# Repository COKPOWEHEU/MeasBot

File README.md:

# MeasBot
Automatization system for measures by scientific devices

Инструкция по тестированию:
=== Linux ===
Запускаете ./prog64 [script]
Если script не указан, будет использован дефолтный data/script.lua

=== Windows ===
Копируете core\res\prog32.exe в mingw_dll\res32.exe с заменой
Копируете в каталог modules\lib\lib\dyn (возможно, понадобится заменить файл dyn каталогом с тем же именем) следующие файлы с заменой имени:
modules\e24\res\prog32.dll -> e24.dll
modules\mygui_gtk\res\prog32.dll -> mygui_gtk.dll
modules\tty\res\prog32.dll -> tty.dll
После чего запускаете mingw_dll\prog32.exe [script]
Если script не указан, будет использован дефолтный data\script.lua

Данный геморрой связан с тем, что программа находится в начальной стадии разработки и особого внимания эргономике не уделялось.

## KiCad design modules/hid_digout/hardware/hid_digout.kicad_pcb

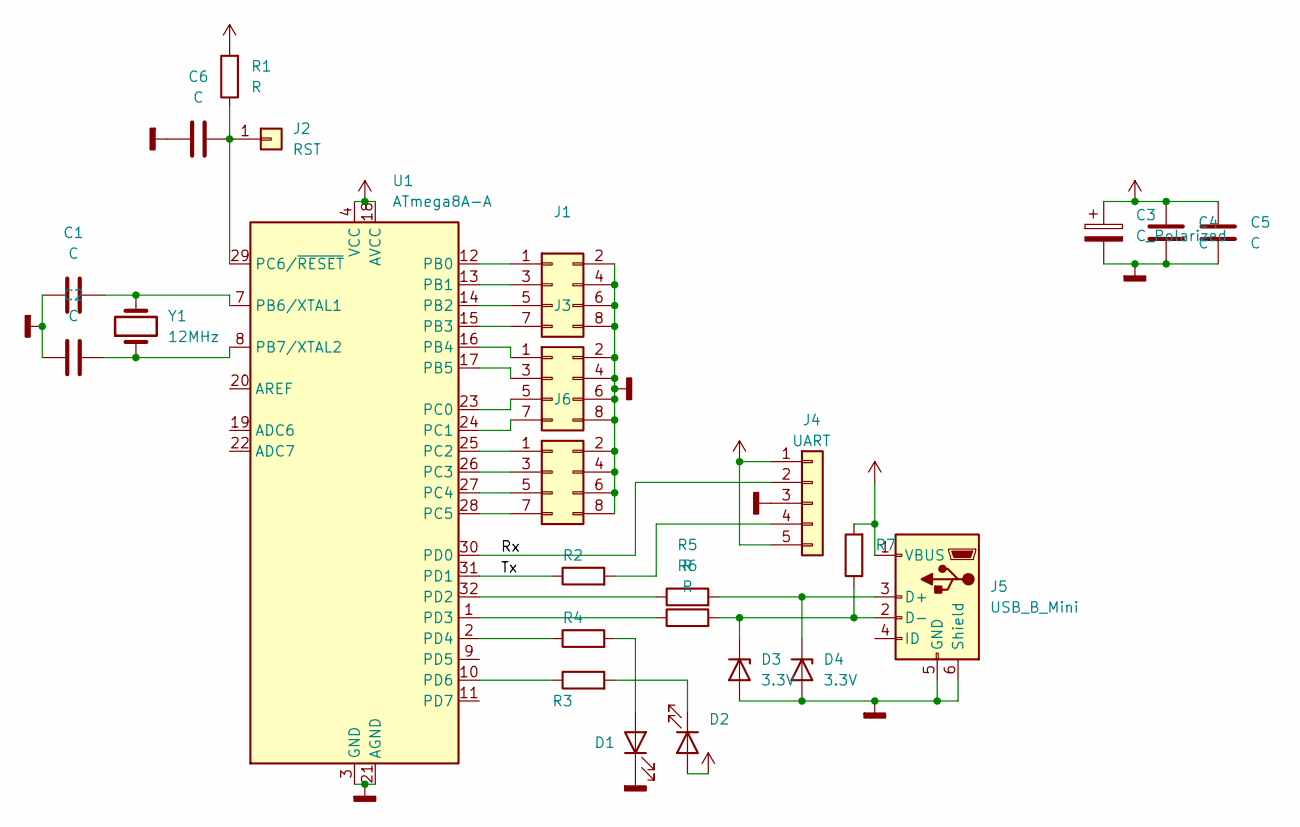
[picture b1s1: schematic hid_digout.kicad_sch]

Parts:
C1, C2: C; C_Disc_D3.4mm_W2.1mm_P2.50mm
C3: C_Polarized; CP_Radial_D10.0mm_P5.00mm
C4, C5: C; C_Disc_D5.0mm_W2.5mm_P5.00mm
C6: C; C_1206_3216Metric
D1, D2: LED; LED_D5.0mm_Horizontal_O3.81mm_Z9.0mm
D3, D4: 3.3V; D_5W_P10.16mm_Horizontal
J1, J3, J6: Conn_02x04_Odd_Even; PinHeader_2x04_P2.54mm_Horizontal
J2: RST; PinHeader_1x01_P2.54mm_Vertical
J4: UART; PinHeader_1x05_P2.54mm_Horizontal
J5: USB_B_Mini; USB-mini
R1, R2, R3, R4, R5, R6, R7: R; R_0805_2012Metric
U1: ATmega8A-A; TQFP-32_7x7mm_P0.8mm
Y1: 12MHz; Crystal_HC49-U_Vertical

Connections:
/Rx: J4.2, U1.30 (PD0)
/Tx: R2.1, U1.31 (PD1)
GNDD: C1.1, C2.1, C3.2, C4.1, C5.1, C6.1, D1.1 (K), D3.2 (A), D4.2 (A), J1.2, J1.4, J1.6, J1.8, J3.2, J3.4, J3.6, J3.8, J4.3, J5.5 (GND), J5.6 (Shield), J6.2, J6.4, J6.6, J6.8, U1.3 (GND), U1.5 (GND), U1.21 (AGND)
unnamed: C1.2, U1.7 (PB6/XTAL1), Y1.2
unnamed: C2.2, U1.8 (PB7/XTAL2), Y1.1
unnamed: D2.1 (K), R3.2
unnamed: D3.1 (K), J5.2 (D-), R6.2, R7.1
unnamed: D4.1 (K), J5.3 (D+), R5.2
unnamed: J4.4, R2.2
unnamed: C6.2, J2.1, R1.1, U1.29 (PC6/~RESET)
unnamed: R3.1, U1.10 (PD6)
unnamed: D1.2 (A), R4.2
unnamed: R5.1, U1.32 (PD2)
unnamed: R6.1, U1.1 (PD3)
unnamed: R4.1, U1.2 (PD4)
unnamed: J1.1, U1.12 (PB0)
unnamed: J1.3, U1.13 (PB1)
unnamed: J1.5, U1.14 (PB2)
unnamed: J1.7, U1.15 (PB3)
unnamed: J3.1, U1.16 (PB4)
unnamed: J3.3, U1.17 (PB5)
unnamed: J3.5, U1.23 (PC0)
unnamed: J3.7, U1.24 (PC1)
unnamed: J6.1, U1.25 (PC2)
unnamed: J6.3, U1.26 (PC3)
unnamed: J6.5, U1.27 (PC4)
unnamed: J6.7, U1.28 (PC5)
VCC: C3.1, C4.2, C5.2, D2.2 (A), J4.1, J4.5, J5.1 (VBUS), R1.2, R7.2, U1.4 (VCC), U1.6 (VCC), U1.18 (AVCC)

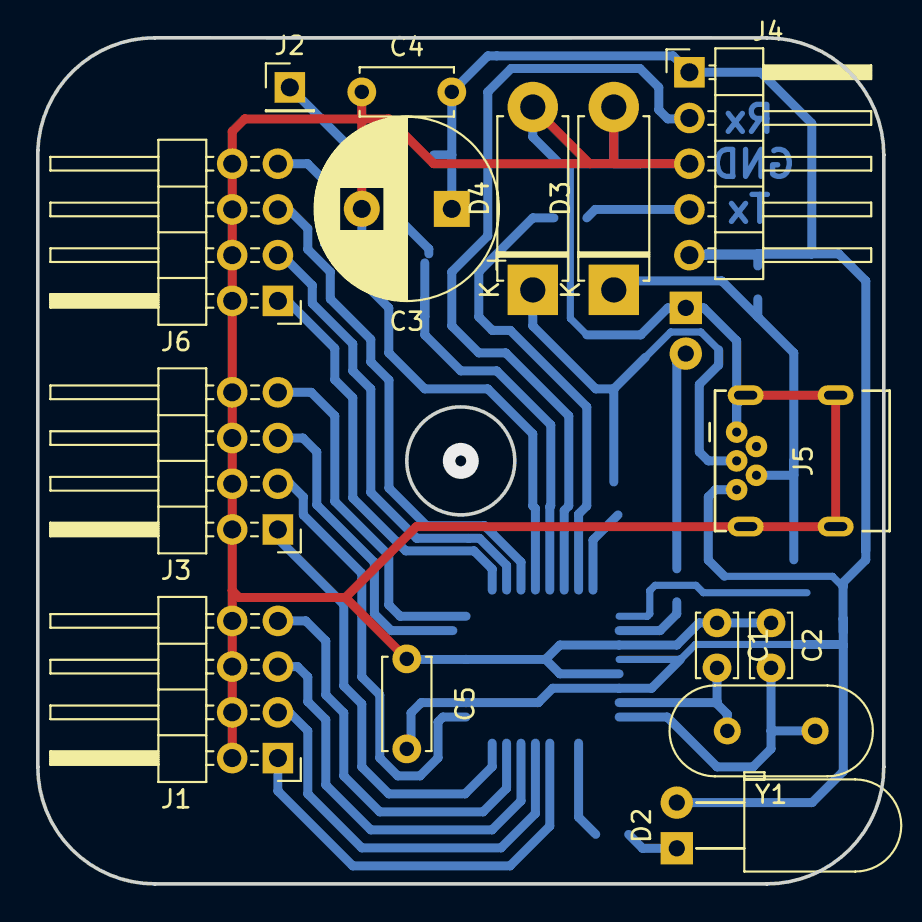
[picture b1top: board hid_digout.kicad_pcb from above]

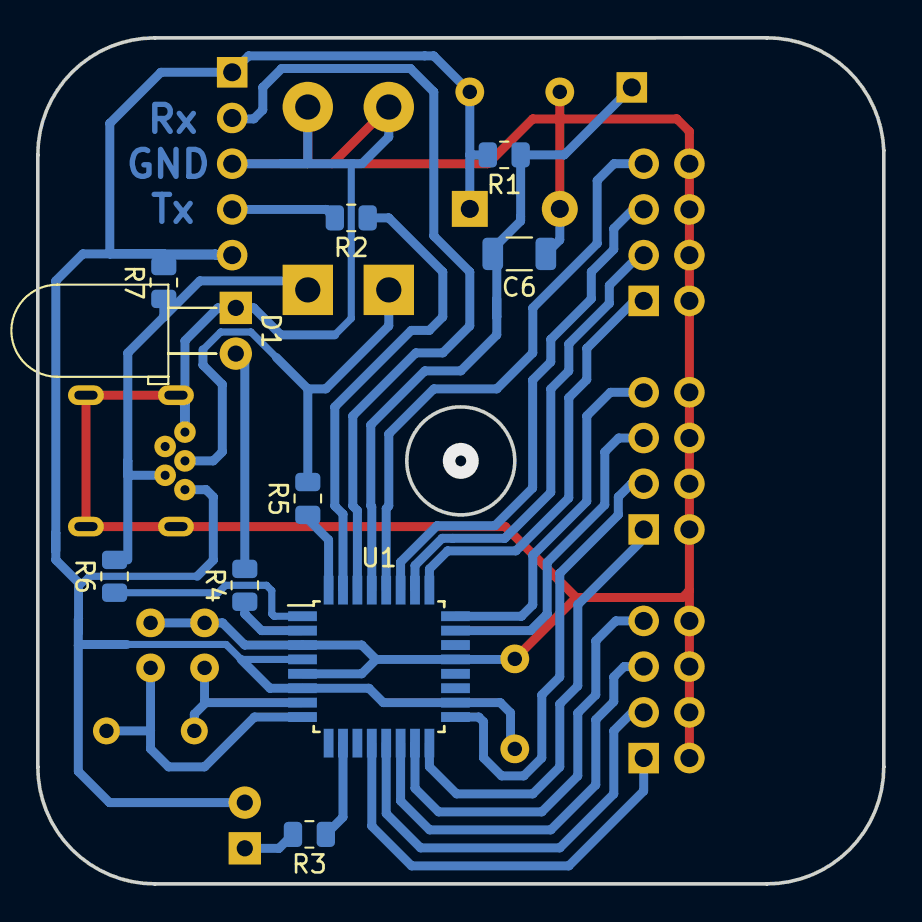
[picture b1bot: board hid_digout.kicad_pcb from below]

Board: 2 copper layers, 47.0 x 47.0 mm, 25 parts (10 on the bottom side), 28 nets.

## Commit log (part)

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2020-03-19 GUI module based on GTK
    first commit: add objects "gui", "button" and "edit" with basic functions
2020-03-22 restructurize architecture. Add links to modules
2020-03-22 move makefile to modules/src
2020-03-22 remove 'doc' from mingw
2020-03-22 Add mygui_gtk
2020-03-22 Fix lua script calling
2020-03-22 Add license file
2020-03-23 fix cplusplus -> __cplusplus
2020-03-23 Add module 'tty' with basic functional
2020-03-23 mygui_gtk: plot: add font scale
2020-03-23 mygui_gtk: plot: fix axis lines and overflow graphic
2020-03-23 mygui_gtk: plot: remove temporary comments
2020-03-24 mygui_gtk: main: add 'static' before Lua functions
2020-03-24 modules: Fix target 'release' to byild ready-to-push configuration
2020-03-24 mygui_gtk: assign all widgets to windows
2020-03-24 mygui_gtk: remove single Mainwindow. Now you can create more than one windows and update() will stops only if all of them are closed
2020-03-24 mygui_gtk: Rename MainWindow -> Gui
2020-03-24 restore sample script 'script.lua'
2020-03-26 add doc; change TODO
2020-03-26 e24: create a folder
2020-03-26 e24: added function of close file
2020-03-26 e24: added function of read from file
2020-03-26 e24: Change function of read and added functions for creating lua module
2020-03-26 e24: added test files and little changes in test.lua
2020-03-28 mygui_gtk: Add radiobutton
2020-03-29 modules:mygui_gtk: Add function 'free_index' to remove element address from gui pool. And thus fixes radiobutton's find on pool
2020-03-30 modules:mygui_gtk: remove lua_State from widgets to global object 'gui'
2020-03-30 modules:mygui_gtk: change 'window' object to raw 'GtkWidget' as container for windgets
2020-03-30 modules:mygui_gtk: remove Radiobutton debug output
2020-03-30 modules:mygui_gtk: remove 'window.h'
2020-03-30 modules:mygui_gtk: Add previous version of TabControl
2020-03-30 modules:mygui_gtk: Add method to remove tabs from TabControl
2020-03-30 e24: Added method readADC()
2020-03-30 e24: Added splitting into 4 separate channels (e24.channel1, ..., e24.channel4) with methods getVoltage and setVoltScale
2020-03-31 e24: Added method readADC() ---modules:e24: without 'build' durectory; add result binary (*.so, *.dll) and their links (COKPOWEHEU)
2020-03-31 e24: Changed implementation of channels from functions in classes
2020-04-01 Update mingw and dlls to lastest gtk version
2020-04-01 modules:mygui_gtk: add ProgressBar
2020-04-01 modules:mygui_gtk Add checkbox
2020-04-01 modules:mygui_gtk: Add SpinEdit
2020-04-01 modules:mygui_gtk:progress: Fix name 'intvars'
2020-04-01 modules:mygui_gtk: Add file open/close dialogs. WARNING! Does not work in windows!
2020-04-01 modules:mygui_gtk: Add message dialogs. WARNING! Does not work in windows!
2020-04-01 modules:mygui_gtk:Progressbar: Fix obj->GTK_LEVEL_BAR(obj)
2020-04-02 Combined functions chn_getVoltage into one getVoltage, the same with chn_setVoltScale (renamed to setRange)
2020-04-02 Changed script of e24
2020-04-02 Restore mingw libraris and mingw_dll. Now 'Dialog' works in both systems, bus 'ProgressBar' broken
2020-04-02 modules:mygui_gtk: Add 'Frame'
2020-04-02 modules:mygui_gtk:all: modify all behaviour to fields by __index, __newindex and __pairs metamethods
2020-04-03 modules:mygui_gtk: Restore 'Progressbar' but it looks rough at both systems
2020-04-03 modules:mygui_gtk: Fix error while changing text on 'Label'
2020-04-03 modules:mugui_gtk: Add documentation and examples
2020-04-19 lps305: Added folder, basic functionality of module and features in doc/lps305.txt
2020-04-19 tty: Added parameter 'mode' to ttym_open function to simplify configuration
2020-04-19 tty: Changed script 'tty'
2020-04-19 lps305: Added source files of lps305, also added functions of connect and close for script. Changed basic script.
2020-04-19 lps305: Added functions with information about the device (getModel, getVersion) and a function that returns the working state (getStatus)
2020-04-19 lps305: Added functions of set and get Voltage
2020-04-19 lps305: Added function of enable/disable output
2020-04-19 lps305: Added function of tracking
2020-04-19 lps305: Added function of enable/disable beeper
2020-04-19 lps305: Added function of setup digital output
2020-04-19 lps305: Added function of setup compensated output
2020-04-19 lps305: Changed documentation
2020-04-23 modules:mygui_gtk:plot. Add properties .cur_x, .cur_y as values of cursor
2020-04-26 e24: Changed return value in function 'L_help'
2020-04-26 lps305: Added source files of lps305 and tty, also added functions of 'connectNewDevice' and 'disconnect' for script.
2020-04-26 lps305: Added functions with information about the device (getModel, getVersion) and a function that returns a commands for working with the device
2020-04-26 lps305: Added table 'pos' for working with positive output and functions for setting output voltage and reading voltage.
2020-04-26 lps305: Added functions for setting output current and reading current.
2020-04-26 lps305: Added functions for setting output current and reading current for 'neg' table.
2020-04-26 lps305: Added table 'both' for working with both outputs and functions for setting output voltage and reading voltage on both channels.
2020-04-26 lps305: Added functions for setting output current and reading current for 'both' table.
2020-04-26 lps305: Changed return value in function 'L_help'
2020-05-26 lps305: Changed conditions for checking input data in function L_connctNewDevice
2020-05-26 lps305: The 'disconnect' function is removed and the '__gc' metafunction is added instead
2020-05-26 lps305: Added table 'both' for working with both outputs and functions for setting output voltage and reading voltage on both channels
2020-05-26 lps305: Fix absolute / relative addressing of table (meta)fields and function parameters
2020-05-26 lps305: make *.so + *.dll demo builds
2020-06-02 tty: fix string input. Remove \r, \n from output string
2020-06-02 mygui_gtk:plot: fix drawing lines without change
2020-06-07 Add log output; restore script for testing GUI
2020-06-07 Add instruction of testing to README
2020-06-22 mygui_gtk: Add 'scroller' widget
2020-06-22 mygui_gtk: Add versions of CheckBox: ToggleButton and SwitchButton
2020-07-15 mygui_gtk: fix output of large values (sprintf format) and overlapping long strings in X-axis
2020-07-15 small modification of global Makefile
2020-07-15 mygui_gtk: fix change locales when initielizing GTK
2020-08-01 lps305: Changed string help in L_help
2020-08-02 sr570: Added folder and basic functionality of module
2020-08-02 sr570: Added functions of reset category
2020-08-02 sr570: Added functions of sensitivity category
2020-08-02 sr570: Added functions of 'offset current' category
2020-08-02 sr570: Added functions of 'filters' category
2020-08-02 sr570: Added functions of 'bias voltage' and 'gain mode' categories
2020-08-02 sr570: Updated 'help' function
2020-08-08 sr570: Added more comments and function for the error log
2020-08-08 sr570 & lps305: Changed helpstring
2020-08-08 sr570: Changed comment of 'setCalOffsetCurrentLVL'
2020-08-09 sr570: Added a function to find the index of a number from a given array of numbers
2020-08-10 SR570: Changes settings of 'sensitivity' and 'offset current' from table to exact value
2020-08-10 SR570: Change 'High' and 'Low' filters from table to exact value
2020-08-10 SR570: Change 'setBiasVoltLVL' from value in millivolts (int) to value in volts (float)
2020-08-10 SR570: rebuild
2020-08-12 sr570: Changed 'setHighFilter' function
2020-08-12 sr570: Changed type of variable
2020-08-12 sr570: Changed parameters at script and cpp files
2020-09-03 sr570: fix bug in settings in 'setLowFilter' from array index to exact value
2020-09-03 sr5105: initial commit
2020-09-04 sr5105: add functions rawSend, getMagPhase, getSens, setSens. Behaviour of measure function changed to return exact value in Si
2020-09-04 sr5105: fix debug output in getMagPhase. Add 3rd parameter (max value) to getXY, getMagPhase
2020-09-04 sr5105: add other methods
2020-09-04 sr5105: Add Help content
2020-09-04 mygui_gtk: fix bug with caption of widgets
2020-09-07 mygui_gtk: SpinEdit: Add optional parameters 'min', 'max', 'digits' to constructor; add gettrt-setter 'digits'; add Call-back function 'OnChange(val)'
2020-09-07 mygui_gtk: scroller: fix bug with names of functions
2020-09-07 mygui_gtk: checkbox: Fix warnings
2020-09-07 sr830: Add basic functionality of module
2020-09-07 sr830: fix source code
2020-09-07 sr830: Add connect and disconnect functions
2020-09-08 Core: catch os.exit function
2020-09-08 sr830: Add initialize functions and other
2020-09-08 sr830: Add functions of setup
2020-09-08 sr830: Add functions of output data and change help string
2020-09-11 mygui_gtk: plot: Change reaction to non-complete tables
2020-09-14 lps305: Fix bug with garbage collecting device; Fix bug with partially read from TTY in Linux
2020-09-14 lps305: return {pos=nil, neg=nil, both=nil} on failure while opening device
2020-09-14 sr830: fix read of data from tty
2020-09-17 sr830: global update
2020-09-20 sr830: delete old C++ version and change it to simpiy C version
2020-09-25 SR830: Makes sub-devices SineOut and SineIn as separated devices into complex SR830 object
2020-09-25 SR830: Fix bug FP_NAN -> NAN
2020-09-25 SR830: add Help
2020-09-25 SR5105: Fix FP_NAN -> NAN
2020-09-25 lps305: add function of setup digital output
2020-09-25 sr830: little fix
2020-09-25 sr830: add script of utilities
2020-09-25 sr830: fix initialization os SRS
2020-09-25 remove executable flag from all ttym.* files
2020-09-25 sr570: add function of get sensitivity
2020-10-05 sr570: Changed types of parameters from lua
2020-10-05 sr570: fix FP_NAN -> NAN
2020-10-06 sr830&sr570: little fixes
2020-10-12 mygui_gtk: Fix bug on close windows. Now they just hide
2020-10-12 add Measure script
2020-10-13 SR830: delete text 'on close' and recompile
2020-10-13 measure: first script (sr830 + sr5105 + sr570)
2020-10-13 mygui_gtk: combobox: Add initialization of element sequence in constructor
2020-10-13 mygui_gtk: window: Add functions 'Show' and 'Hide'
2020-10-13 mygui_gtk: window: add 'visible' property
2020-10-13 mygui_gtk: add 'MainWindow'
2020-10-14 mygui_gtk.Combobox: Add 'SelectedItem' method
2020-10-14 mygui_gtk.Combobox: return elements as fields of class. combobox[1], combobox[2], ...
2020-10-14 scripts: change utils
2020-10-14 e24: switch e24 from dummy to real device
2020-10-15 Add instruction of identifying of USB-RS232 convertors
2020-10-15 LPS305: return nil on error instead of FakeTable
2020-10-15 mygui_gtk:all - add actual read of widgets size
2020-10-15 mygui_gtk:spinedit: Add 'step' to constructor
2020-10-16 mygui_gtk:edit: Add 'OnEnter(str)' callback
2020-10-21 Timer: initial commit
2020-10-29 Timer: work in progress
2020-10-30 Timer: some functions works! CreateCallbacks, Sleep etc
2020-10-30 Timer: Add function 'GetSysTime'
2020-11-02 Timer: 'require' option returns singletone now
2020-11-02 Timer: remove table 'self' from all functions
2020-11-02 Timer: Add 'UnregisterCallback' function
2020-11-02 Timer: change global callback counter 'timer_cbc_num' to field of structure
2020-11-02 Timer: Fix (workaround) bug with recursive callback function call
2020-11-10 mygui_gtk.plot: move plot lines to upper plane
2020-11-10 mygui_gtk.plot: fix grid drawing
2020-11-10 mygui_gtk.plot: fix drawing of axis numbers
2020-11-17 lps305, sr*: little fixes initialize of current and fix 'val' at findCeilInArr
2020-11-18 meas-oleg: Description of the experiment with comments
2020-11-18 utils: Added comments
2021-01-19 meas-oleg: Changed magnet ratio of getField
2021-05-30 meas-oleg: added measure2
2021-12-24 Add description of GTK module
2022-10-02 Add examples
2022-10-02 Add test for sr830_async
2022-10-02 Add width/height to label, fix negative size error while resizeing Label and Edit
2022-10-02 Small fixes
2022-10-13 Add Hid digout module
2022-10-13 AKIP_114x: small fixes
2022-10-20 Hid digout: Add hardware - pcb and firmware
2023-01-27 Add 'fixlinks' script to fix symlinks after repo copy
2023-01-31 AKIP_114x: fix float format when setting voltage, current etc
